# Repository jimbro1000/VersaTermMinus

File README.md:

# VersaTermMinus

Reduced and simplified version of David Hansel's VersaTerm
project [github.com/dhansel/VersaTerm](https://github.com/dhansel/VersaTerm)

You can order PCBs for this project direct from PCBWay's shared projects
(https://www.pcbway.com/project/shareproject/VersaTermMinus_d8ad71ad.html)

## Changes to the Original Design

There are four significant changes to the board:

1. The barrel-jack power supply connection is deleted
2. The USB socket for keyboard is now micro-USB
3. The MAX3232 is integrated into the board
4. Where possible components are SMD

The changes allow the board to be reduced in size and cost.

## Assembly

It is highly recommended to use a stencil and
hot plate for mounting the SMD components. If
assembling by hand, start with the MAX232 chip
and resistor pack. It is important to mount the
small resistors, capacitors and diodes before
adding the HDMI, USB and large through-hole
components. Failing to do those first will make
assembly much harder.

If you want to use the USB keyboard option a
pair of wires needs to be attached to TP2 and
TP3 on the underside of the Pico board, and
connected to the J2 position on the main board.
Pin 1 of J2 should be connected to TP2.

### 1n4148 Diodes

The board uses a regular 0805 footprint for the
smaller 1n4148 diodes but it may prove easier
to source SOD323. These still fit easily on the
0805 footprint.

## Firmware

The pico board should be loaded with the 
original VersaTerm firmware from David Hansel's
git repository: [VersaTerm uf2 firmware](https://github.com/dhansel/VersaTerm/blob/main/software/VersaTerm.uf2)

## Errors on Early Fabricated Boards

On the first run of the board the traces to
the RS232 DE9 connector were incorrect. To fix
the error it is necessary to cut three of the
traces running from the MAX232 chip to the DE9.

With the DE9 nearest you the top three diagonal
traces running from top right to bottom left
need to be cut.

Three wires then need soldering to the upper two
pins of the DE9 and the lower middle (Pins 2, 3
and 8 of the connector). These need to be wired
to the MAX3232 on pins 5, 15 and 16.

DE9 pin 8 -> MAX3232 pin 16  
DE9 pin 2 -> MAX3232 pin 5  
DE9 pin 3 -> MAX3232 pin 15

To keep the fix tidy I drilled a hold through
the PCB above the right hand edge of the DE9
and below the visible traces on the top of the
board. This allows shorter, more direct
connections to be made.

A second fault exists within the buzzer circuit.
The polarity marking for the buzzer is reversed
(just fit the buzzer back to front). The transistor
switching the buzzer is also incorrect. To fix this
the transistor needs rotating around the top left 
pad (pin 2) such that the top right pin (1) sits on
the bottom pad. A wire needs to be run from the now
loose pin of the transistor (pin 3) to the negative
side of the buzzer, the vacant transistor pad or
the top pad of D1. The trace running from transistor
to the buzzer could be exposed to allow a solder 
bridge to be created

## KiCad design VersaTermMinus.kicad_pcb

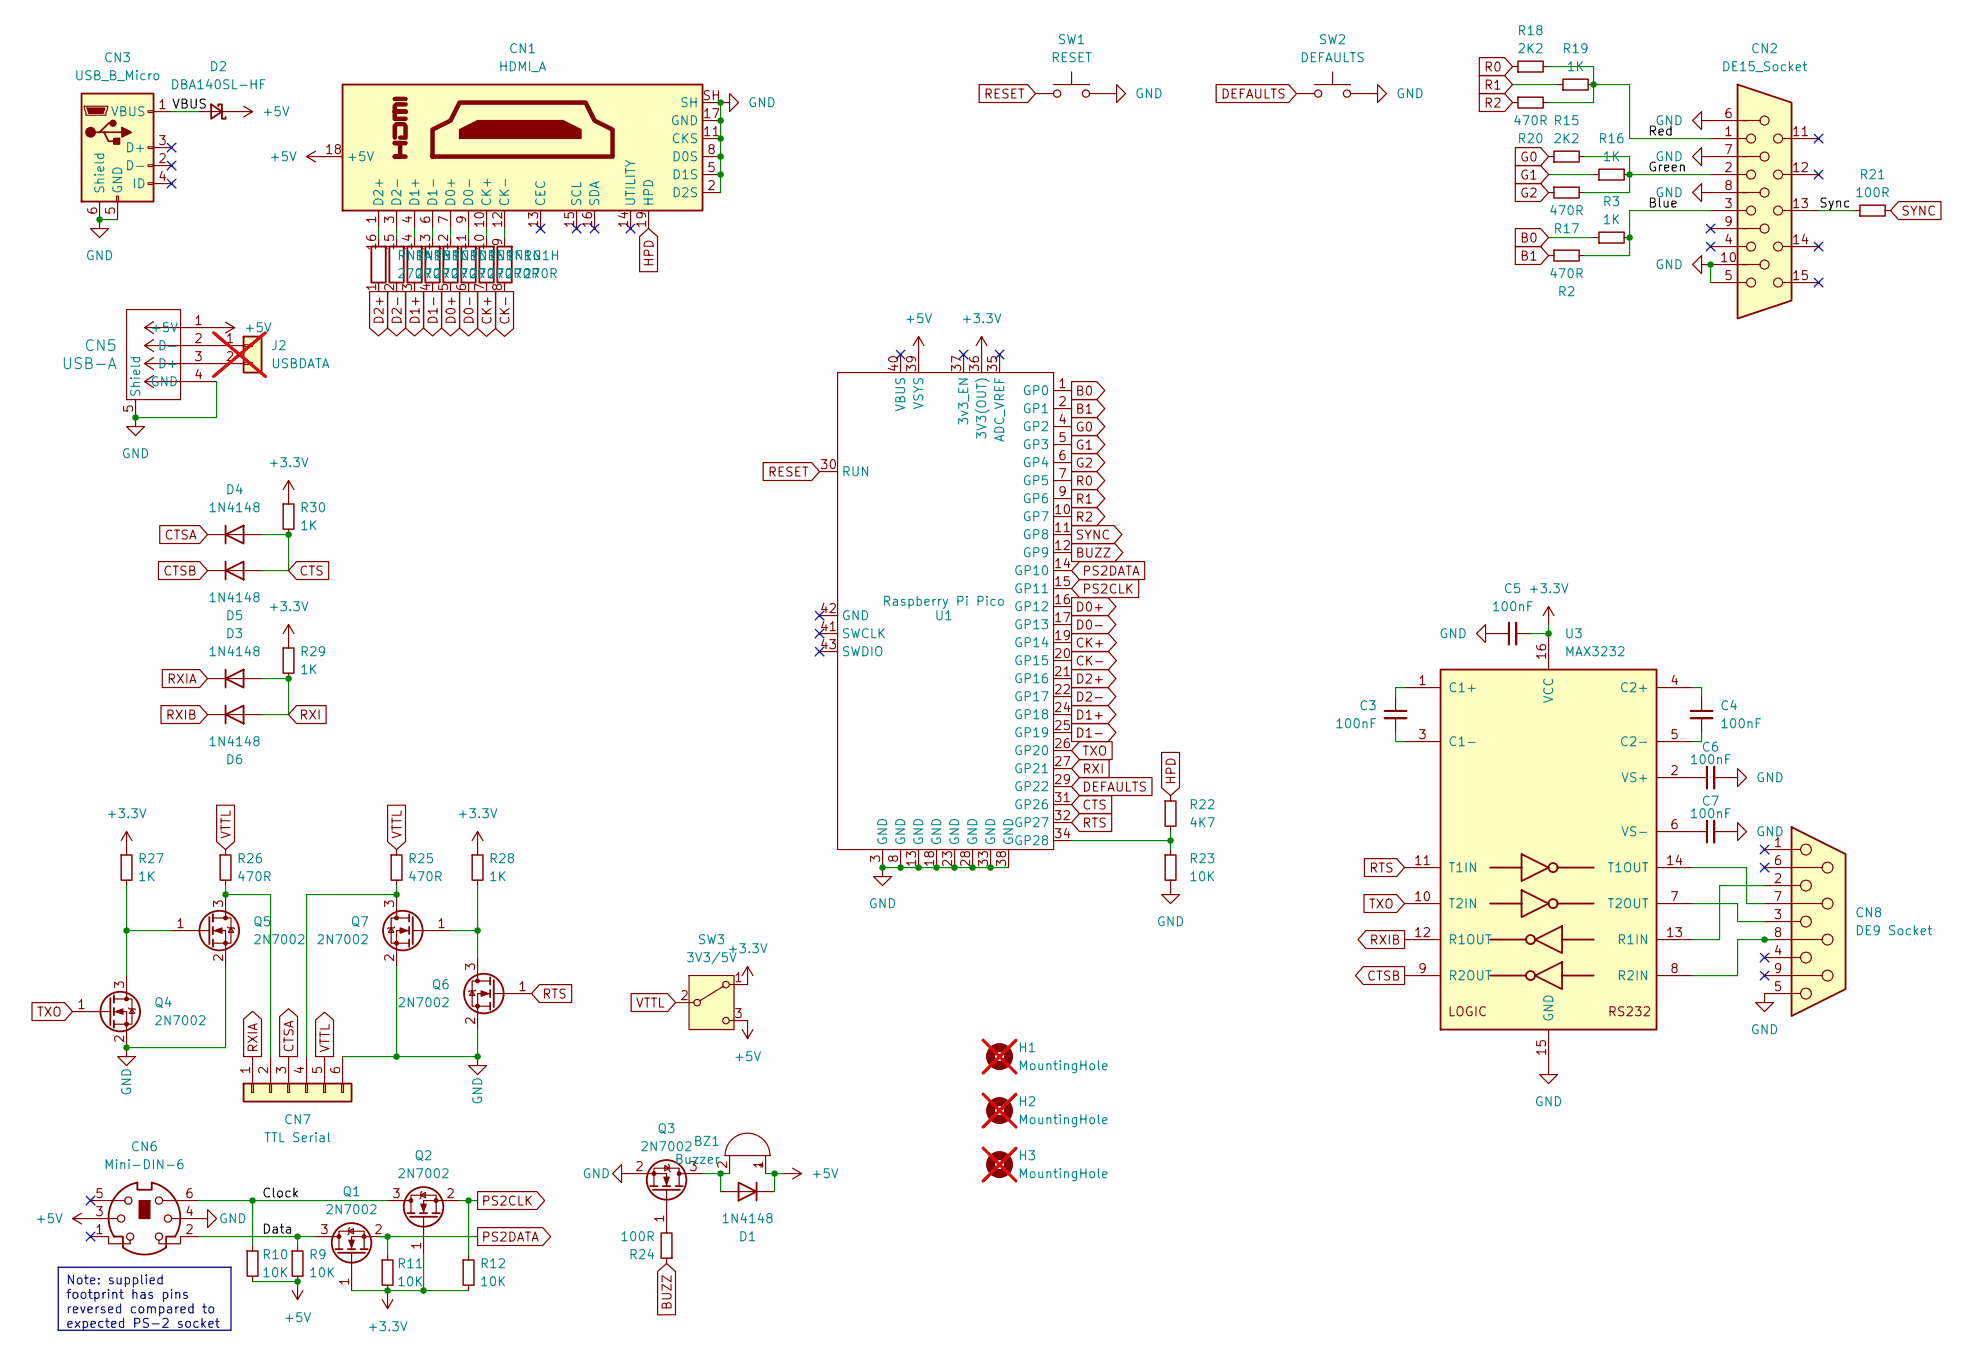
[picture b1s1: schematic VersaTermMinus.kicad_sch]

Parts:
BZ1: Buzzer; Buzzer_12x9.5RM7.6; LCSC C96491
C3, C4, C5, C6, C7: 100nF; C_0805_2012Metric_Pad1.18x1.45mm_HandSolder; DigiKey 311-1140-1-ND
CN1: HDMI_A; HDMI_A_Amphenol_10029449-x01xLF_Horizontal; DigiKey 609-4614-1-ND
CN2: DE15_Socket; DSUB-15-HD_Female_Horizontal_P2.29x1.98mm_EdgePinOffset3.03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; DigiKey L77HDE15SD1CH4FVGA-ND
CN3: USB_B_Micro; USB_Micro-B_Wuerth_629105150521; DigiKey 732-5960-1-ND
CN5: USB-A; CONN_67643-2911_MOL; DigiKey WM4078-ND
CN6: Mini-DIN-6; KMDGX-6S-N; DigiKey 2092-KMDGX-6S-BS-ND
CN7: TTL Serial; PinHeader_1x06_P2.54mm_Horizontal; LCSC C492414
CN8: DE9 Socket; DSUB-9_Male_Horizontal_P2.77x2.84mm_EdgePinOffset4.94mm_Hou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; DigiKey AE10968-ND
D1, D3, D4, D5, D6: 1N4148; D_0805_2012Metric_Pad1.15x1.40mm_HandSolder; DigiKey 1N4148WXTPMSCT-ND
D2: DBA140SL-HF; D_SMA_Handsoldering; DigiKey 641-1762-1-ND
H1, H2, H3: MountingHole; MountingHole_3.2mm_M3; not fitted
J2: USBDATA; PinHeader_1x02_P2.54mm_Vertical; not fitted
Q1, Q2, Q3, Q4, Q5, Q6, Q7: 2N7002; SOT-23; DigiKey 2N7002NCT-ND
R2, R17, R20, R25, R26: 470R; R_0805_2012Metric_Pad1.20x1.40mm_HandSolder; DigiKey RMCF0805FT470RCT-ND
R3, R16, R19, R27, R28, R29, R30: 1K; R_0805_2012Metric_Pad1.20x1.40mm_HandSolder; LCSC C95781
R9, R10, R11, R12, R23: 10K; R_0805_2012Metric_Pad1.20x1.40mm_HandSolder; LCSC C17414
R15, R18: 2K2; R_0805_2012Metric_Pad1.20x1.40mm_HandSolder; LCSC C17520
R21, R24: 100R; R_0805_2012Metric_Pad1.20x1.40mm_HandSolder; LCSC C105577
R22: 4K7; R_0805_2012Metric_Pad1.20x1.40mm_HandSolder; LCSC C17673
RN1: 270R; SOIC-16W_5.3x10.2mm_P1.27mm; DigiKey 4816P-1-271LFCT-ND
SW1: RESET; SW_Tactile_Straight_KSA0Axx1LFTR; DigiKey CKN10734-ND
SW2: DEFAULTS; SW_Tactile_Straight_KSA0Axx1LFTR; DigiKey CKN10734-ND
SW3: 3V3/5V; SW_Slide_SPDT_Angled_CK_OS102011MA1Q; DigiKey CKN9559-ND
U1: Raspberry Pi Pico; RPi_Pico_SMD_TH
U3: MAX3232; SOIC-16_3.9x9.9mm_P1.27mm; DigiKey 296-13094-1-ND

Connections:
+3.3V: C5.2, Q1.1 (G), Q2.1 (G), R11.2, R12.2, R27.1, R28.1, R29.1, R30.1, SW3.1 (A), U1.36 (3V3(OUT)), U3.16 (VCC)
+5V: BZ1.1 (+), CN1.18 (+5V), CN5.1 (+5V), CN6.3, D1.1 (K), D2.1 (K), R9.2, R10.2, SW3.3 (C), U1.39 (VSYS)
/Blue: CN2.3, R2.2, R3.2
/Clock: CN6.6, Q2.3 (D), R10.1
/Data: CN6.2, Q1.3 (D), R9.1
/Green: CN2.2, R15.2, R16.2, R17.2
/Red: CN2.1, R18.2, R19.2, R20.2
/Sync: CN2.13, R21.1
/VBUS: CN3.1 (VBUS), D2.2 (A)
B0: R3.1, U1.1 (GP0)
B1: R2.1, U1.2 (GP1)
BUZZ: R24.1, U1.12 (GP9)
CK+: RN1.7 (R7.1), U1.19 (GP14)
CK-: RN1.8 (R8.1), U1.20 (GP15)
CTS: D4.2 (A), D5.2 (A), R30.2, U1.31 (GP26)
CTSA: CN7.3, D4.1 (K)
CTSB: D5.1 (K), U3.9 (R2OUT)
D0+: RN1.5 (R5.1), U1.16 (GP12)
D0-: RN1.6 (R6.1), U1.17 (GP13)
D1+: RN1.3 (R3.1), U1.24 (GP18)
D1-: RN1.4 (R4.1), U1.25 (GP19)
D2+: RN1.1 (R1.1), U1.21 (GP16)
D2-: RN1.2 (R2.1), U1.22 (GP17)
DEFAULTS: SW2.1, U1.29 (GP22)
G0: R15.1, U1.4 (GP2)
G1: R16.1, U1.5 (GP3)
G2: R17.1, U1.6 (GP4)
GND: C5.1, C6.2, C7.2, CN1.2 (D2S), CN1.5 (D1S), CN1.8 (D0S), CN1.11 (CKS), CN1.17 (GND), CN1.SH, CN2.5, CN2.6, CN2.7, CN2.8, CN2.10, CN3.5 (GND), CN3.6 (Shield), CN5.4 (GND), CN5.5 (Shield), CN6.4, CN7.6, CN8.5, Q3.2 (S), Q4.2 (S), Q5.2 (S), Q6.2 (S), Q7.2 (S), R23.2, SW1.2, SW2.2, U1.3 (GND), U1.8 (GND), U1.13 (GND), U1.18 (GND), U1.23 (GND), U1.28 (GND), U1.33 (GND), U1.38 (GND), U3.15 (GND)
HPD: CN1.19 (HPD), R22.1
unnamed: BZ1.2 (-), D1.2 (A), Q3.3 (D)
unnamed: CN1.10 (CK+), RN1.10 (R7.2)
unnamed: CN1.12 (CK-), RN1.9 (R8.2)
unnamed: CN1.7 (D0+), RN1.12 (R5.2)
unnamed: CN1.9 (D0-), RN1.11 (R6.2)
unnamed: CN1.4 (D1+), RN1.14 (R3.2)
unnamed: CN1.6 (D1-), RN1.13 (R4.2)
unnamed: CN1.1 (D2+), RN1.16 (R1.2)
unnamed: CN1.3 (D2-), RN1.15 (R2.2)
unnamed: CN5.3 (D+), J2.2
unnamed: CN5.2 (D-), J2.1
unnamed: CN7.2, Q5.3 (D), R26.2
unnamed: CN7.4, Q7.3 (D), R25.2
unnamed: Q3.1 (G), R24.2
unnamed: Q4.3 (D), Q5.1 (G), R27.2
unnamed: Q6.3 (D), Q7.1 (G), R28.2
unnamed: R22.2, R23.1, U1.34 (GP28)
unnamed: C3.1, U3.1 (C1+)
unnamed: C3.2, U3.3 (C1-)
unnamed: C4.1, U3.4 (C2+)
unnamed: C4.2, U3.5 (C2-)
unnamed: CN8.2, U3.13 (R1IN)
unnamed: CN8.8, U3.8 (R2IN)
unnamed: CN8.7, U3.14 (T1OUT)
unnamed: CN8.3, U3.7 (T2OUT)
unnamed: C6.1, U3.2 (VS+)
unnamed: C7.1, U3.6 (VS-)
PS2CLK: Q2.2 (S), R12.1, U1.15 (GP11)
PS2DATA: Q1.2 (S), R11.1, U1.14 (GP10)
R0: R18.1, U1.7 (GP5)
R1: R19.1, U1.9 (GP6)
R2: R20.1, U1.10 (GP7)
RESET: SW1.1, U1.30 (RUN)
RTS: Q6.1 (G), U1.32 (GP27), U3.11 (T1IN)
RXI: D3.2 (A), D6.2 (A), R29.2, U1.27 (GP21)
RXIA: CN7.1, D3.1 (K)
RXIB: D6.1 (K), U3.12 (R1OUT)
SYNC: R21.2, U1.11 (GP8)
TXO: Q4.1 (G), U1.26 (GP20), U3.10 (T2IN)
VTTL: CN7.5, R25.1, R26.1, SW3.2 (B)

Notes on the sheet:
Note: supplied footprint has pins reversed compared to expected PS-2 socket

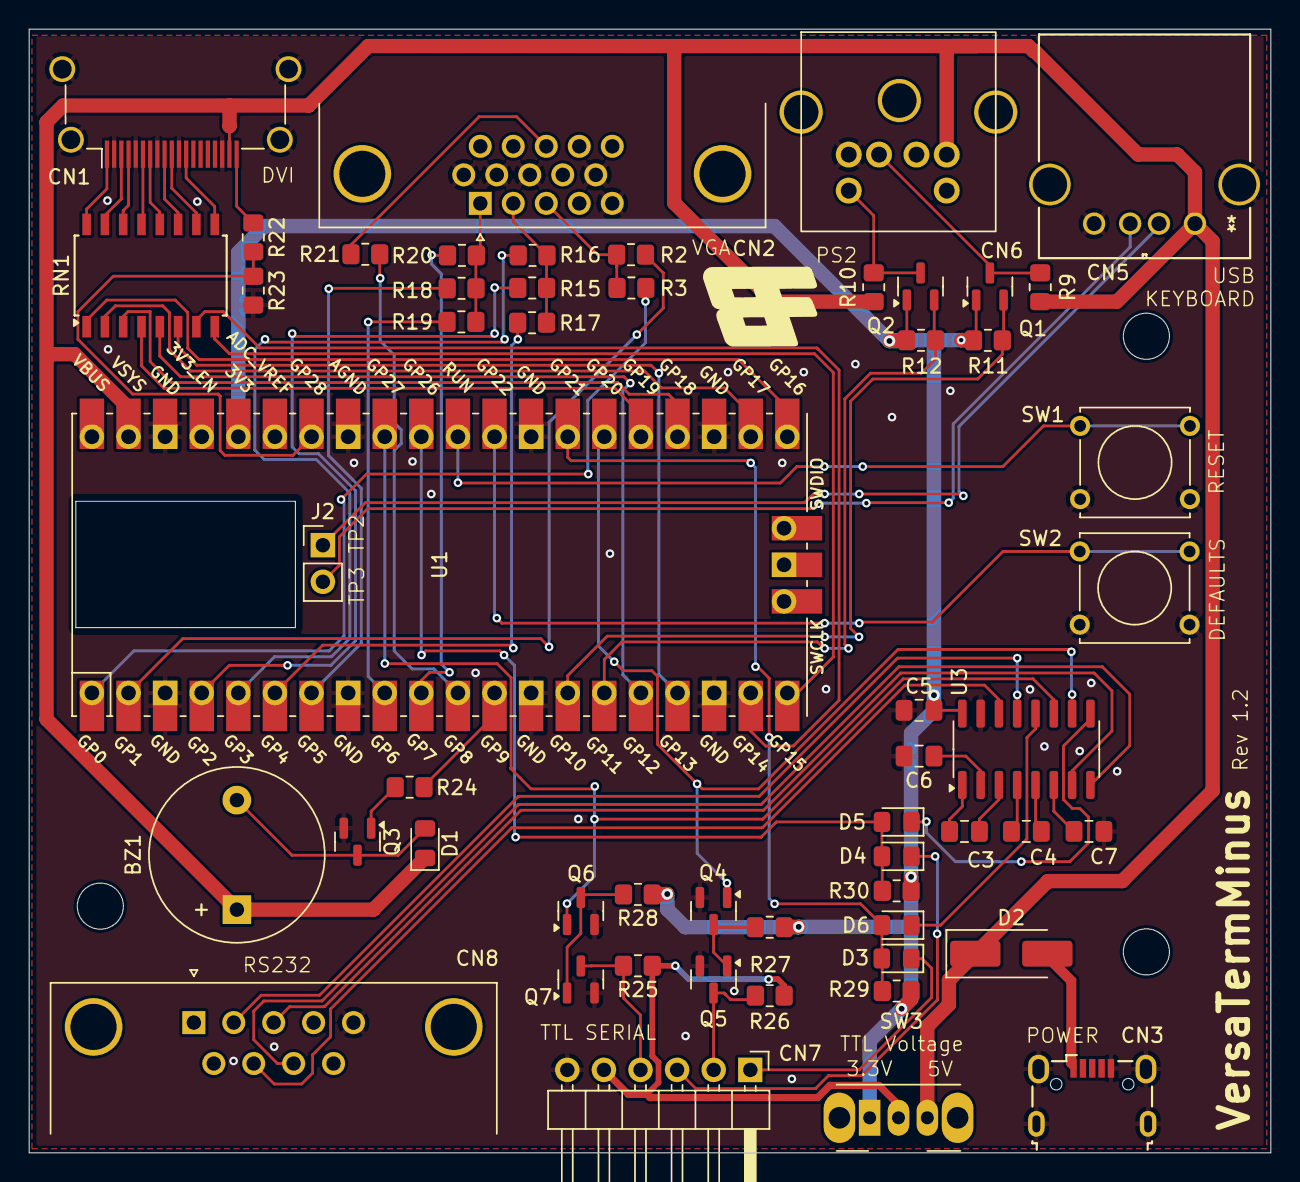
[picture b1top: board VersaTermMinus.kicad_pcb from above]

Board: 2 copper layers, 86.2 x 78.0 mm, 58 parts (0 on the bottom side), 69 nets.

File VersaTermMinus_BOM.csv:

"Reference","Value","Datasheet","Footprint","Qty","DNP"
"BZ1","Buzzer","~","Buzzer_Beeper:Buzzer_12x9.5RM7.6","1",""
"C3,C4,C5,C6,C7","100nF","~","Capacitor_SMD:C_0805_2012Metric_Pad1.18x1.45mm_HandSolder","5",""
"CN1","HDMI_A","https://en.wikipedia.org/wiki/HDMI","Connector_HDMI:HDMI_A_Amphenol_10029449-x01xLF_Horizontal","1",""
"CN2","DE15_Socket","~","Connector_Dsub:DSUB-15-HD_Female_Horizontal_P2.29x1.98mm_EdgePinOffset3.03mm_Housed_MountingHolesOffset4.94mm","1",""
"CN3","USB_B_Micro","https://www.we-online.com/katalog/datasheet/629105150521.pdf","Connector_USB:USB_Micro-B_Wuerth_629105150521","1",""
"CN5","USB-A","676432911","Connector_USBA_Molex:CONN_67643-2911_MOL","1",""
"CN6","Mini-DIN-6","http://service.powerdynamics.com/ec/Catalog17/Section%2011.pdf","Connector_Mini_DIN:KMDGX-6S-N","1",""
"CN7","TTL Serial","~","Connector_PinHeader_2.54mm:PinHeader_1x06_P2.54mm_Horizontal","1",""
"CN8","DE9 Socket","~","Connector_Dsub:DSUB-9_Male_Horizontal_P2.77x2.84mm_EdgePinOffset4.94mm_Housed_MountingHolesOffset7.48mm","1",""
"D1,D3,D4,D5,D6","1N4148","https://assets.nexperia.com/documents/data-sheet/1N4148_1N4448.pdf","Diode_SMD:D_0805_2012Metric_Pad1.15x1.40mm_HandSolder","5",""
"D2","DBA140SL-HF","~","Diode_SMD:D_SMA_Handsoldering","1",""
"J2","USBDATA","~","Connector_PinHeader_2.54mm:PinHeader_1x02_P2.54mm_Vertical","1",""
"Q1,Q2,Q3,Q4,Q5,Q6,Q7","2N7002","https://www.onsemi.com/pub/Collateral/NDS7002A-D.PDF","Package_TO_SOT_SMD:SOT-23","7",""
"R2,R17,R20,R25,R26","470R","~","Resistor_SMD:R_0805_2012Metric_Pad1.20x1.40mm_HandSolder","5",""
"R3,R16,R19,R27,R28,R29,R30","1K","~","Resistor_SMD:R_0805_2012Metric_Pad1.20x1.40mm_HandSolder","7",""
"R9,R10,R11,R12,R23","10K","~","Resistor_SMD:R_0805_2012Metric_Pad1.20x1.40mm_HandSolder","5",""
"R15,R18","2K2","~","Resistor_SMD:R_0805_2012Metric_Pad1.20x1.40mm_HandSolder","2",""
"R21,R24","100R","~","Resistor_SMD:R_0805_2012Metric_Pad1.20x1.40mm_HandSolder","2",""
"R22","4K7","~","Resistor_SMD:R_0805_2012Metric_Pad1.20x1.40mm_HandSolder","1",""
"RN1","270R","https://www.bourns.com/docs/Product-Datasheets/4800P.pdf","Package_SO:SOIC-16W_5.3x10.2mm_P1.27mm","1",""
"SW1","RESET","https://www.ckswitches.com/media/1457/ksa_ksl.pdf","Button_Switch_THT:SW_Tactile_Straight_KSA0Axx1LFTR","1",""
"SW2","DEFAULTS","https://www.ckswitches.com/media/1457/ksa_ksl.pdf","Button_Switch_THT:SW_Tactile_Straight_KSA0Axx1LFTR","1",""
"SW3","3V3/5V","https://www.ckswitches.com/media/1428/os.pdf","Button_Switch_THT:SW_Slide_SPDT_Angled_CK_OS102011MA1Q","1",""
"U1","Raspberry Pi Pico","","MCU_RaspberryPi_and_Boards:RPi_Pico_SMD_TH","1",""
"U3","MAX3232","https://datasheets.maximintegrated.com/en/ds/MAX3222-MAX3241.pdf","Package_SO:SOIC-16_3.9x9.9mm_P1.27mm","1",""

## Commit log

2024-06-09 add silkscreen labelling
2024-06-20 record digikey part numbers
2024-06-20 update fields on pcb
2024-07-01 Add README
2024-07-02 fix de9 and buzzer
2024-07-03 Update renders
2024-07-09 populate missing BOM fields
2024-07-12 fix incorrect schema symbols for 2n7002 transistors
2025-02-19 version 1.1
2025-02-19 update board renders
2025-02-26 add TP labels to back silkscreen
2025-02-26 remove ambiguous drill holes
2025-03-08 update BOM supplier part numbers
